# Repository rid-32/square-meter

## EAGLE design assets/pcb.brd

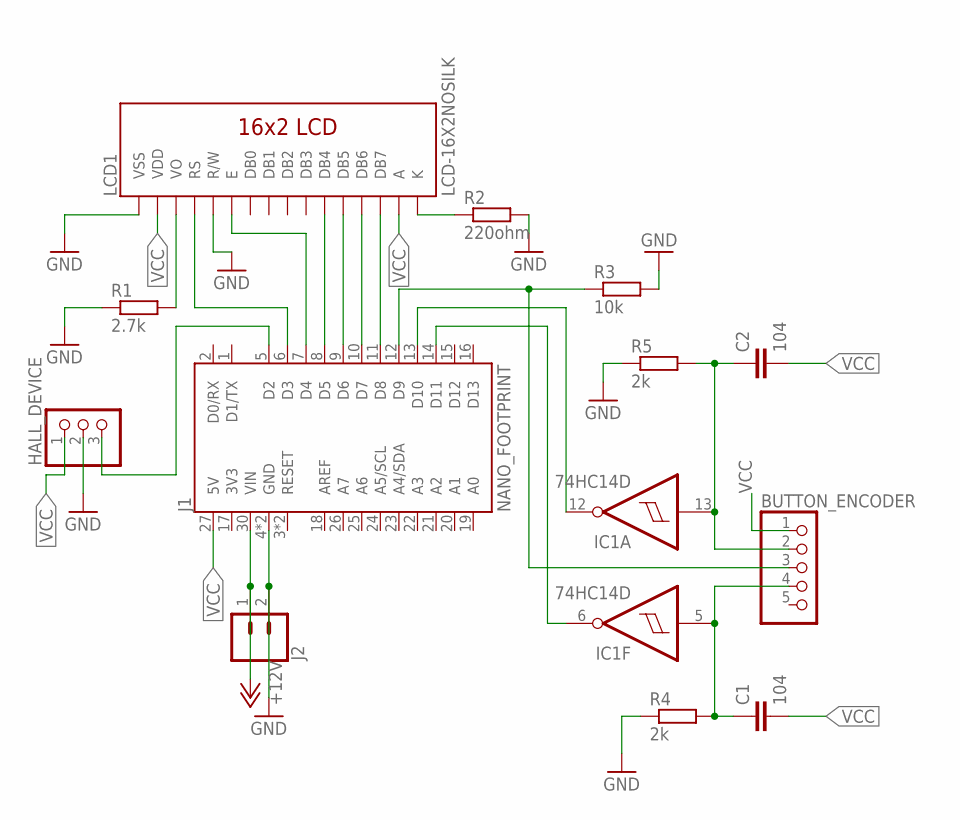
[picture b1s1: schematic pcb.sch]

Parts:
BUTTON_ENCODER: PINHD-1X5; 1X05
C1, C2: 104; C0805
HALL_DEVICE: PINHD-1X3; 1X03
IC1: 74HC14D; SO14
J1: NANO_FOOTPRINT; NANO
J2: CONN_02; 1X02
LCD1: LCD-16X2NOSILK; LCD-16X2_NOSILK
R1: 2.7k; R0805
R2: 220ohm; R0805
R3: 10k; R0805
R4, R5: 2k; R0805

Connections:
+12V: J1.30 (VIN), J2.1
GND: HALL_DEVICE.2, IC1.7 (GND), J1.4 (GND), J1.29 (GND), J2.2, LCD1.1 (VSS), LCD1.5 (R/W), R1.1, R2.2, R3.2, R4.1, R5.1
unnamed: LCD1.3 (VO), R1.2
unnamed: LCD1.16 (K), R2.1
unnamed: J1.11 (D8), LCD1.14 (DB7)
unnamed: J1.10 (D7), LCD1.13 (DB6)
unnamed: J1.9 (D6), LCD1.12 (DB5)
unnamed: J1.8 (D5), LCD1.11 (DB4)
unnamed: J1.7 (D4), LCD1.6 (E)
unnamed: J1.6 (D3), LCD1.4 (RS)
unnamed: HALL_DEVICE.3, J1.5 (D2)
unnamed: BUTTON_ENCODER.3, J1.12 (D9), R3.1
unnamed: IC1.12 (O), J1.13 (D10)
unnamed: IC1.6 (O), J1.14 (D11)
unnamed: BUTTON_ENCODER.2, C2.1, IC1.13 (I), R5.2
unnamed: BUTTON_ENCODER.4, C1.1, IC1.5 (I), R4.2
VCC: BUTTON_ENCODER.1, C1.2, C2.2, HALL_DEVICE.1, IC1.14 (VCC), J1.27 (5V), LCD1.2 (VDD), LCD1.15 (A)

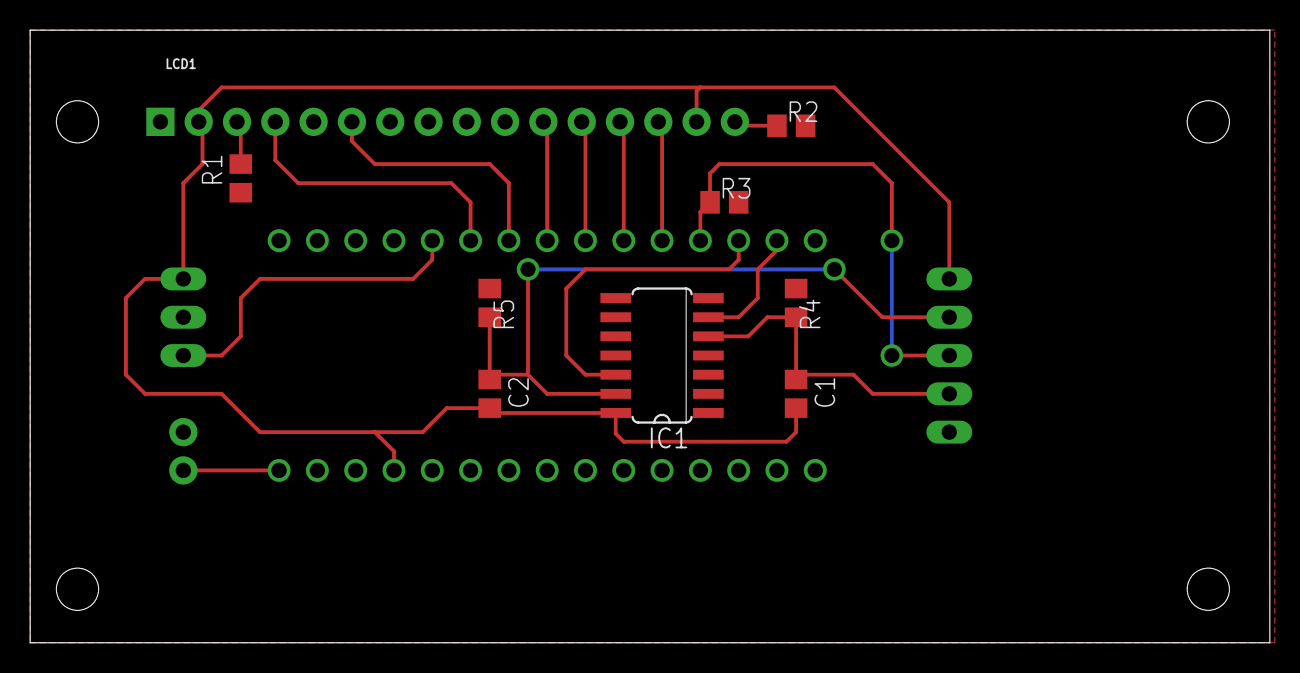
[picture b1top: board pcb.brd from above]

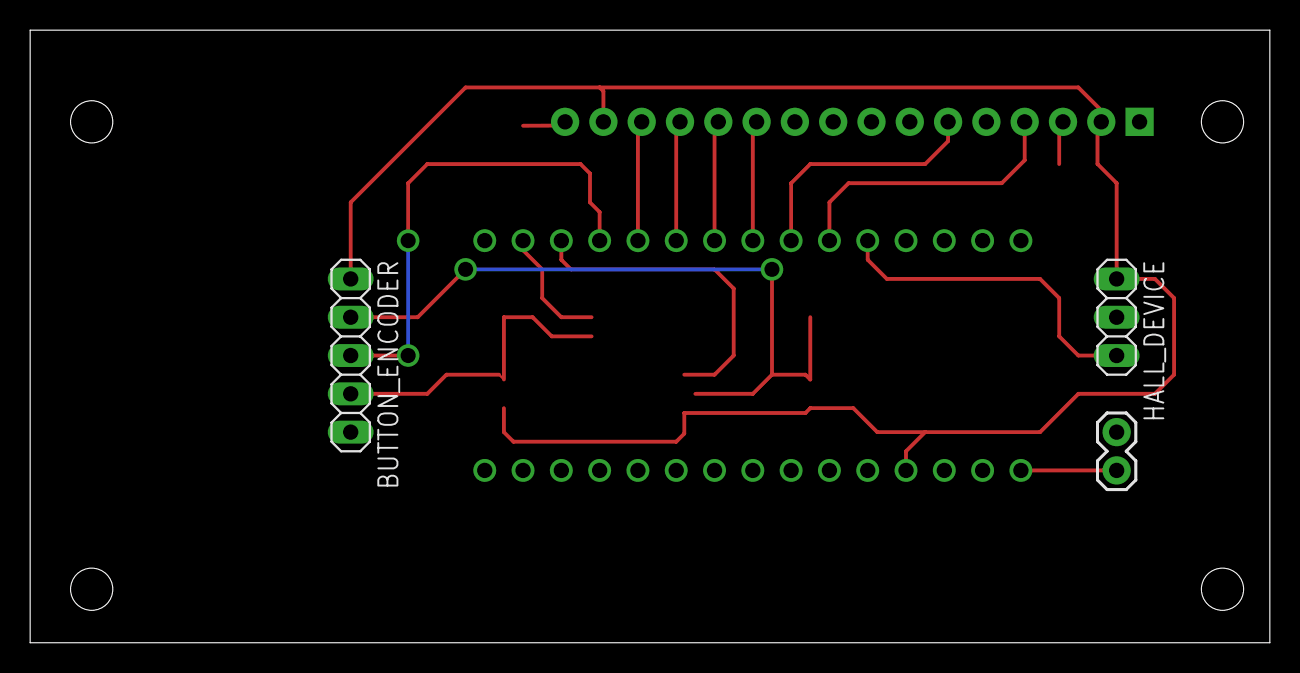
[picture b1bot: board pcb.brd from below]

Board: 2 copper layers, 82.2 x 40.6 mm, 13 parts (4 on the bottom side), 17 nets.

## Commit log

2020-04-20 add button and encoder
2020-04-26 add settings page rendering
2020-04-28 add counters incrementing
2020-04-29 move Page class to the lib
2020-05-12 add components abstract class
2020-05-12 add precise counter
2020-05-13 add precise calculations
2020-05-13 add home page and component force update
2020-05-13 add reset component
2020-05-14 add page events capturing
2020-05-14 remove render from Page scroll method
2020-05-18 add correct pages rendering after navigation
2020-05-18 complete navigation
2020-05-23 add components module
2020-05-23 add settings saving to EEPROM
2020-05-24 add area value to eeprom
2020-05-24 hotfix
2020-06-02 complete device
2020-07-23 add schema and pcb
2020-07-23 add schema and pcb assets
2020-09-12 fix calculations
2021-05-11 add rotations counting from HALL

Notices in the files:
parts and their libraries:
SparkFun-Boards: Licensing: Creative Commons ShareAlike 4.0 International - https://creativecommons.org/licenses/by-sa/4.0
